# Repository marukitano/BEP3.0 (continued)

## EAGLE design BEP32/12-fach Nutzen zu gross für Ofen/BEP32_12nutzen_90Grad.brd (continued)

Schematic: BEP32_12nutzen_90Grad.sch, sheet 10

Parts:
6V1001, 10V1001: TPSB2.0; B2.0
19, 20: 2081-1132; 12-PIN
C1001: 4.7u; C0805
C1002, C1010: 100nF; C0805
C1003, C1004: 100nF,; C0805
C1005, C1006: 100nF.; C0805
C1007, C1008: 100u; C1206
C1009: 2.2nF; C0805
D1001: SM6T; DO214AA
D1002, D1003: 1N4007,; DO-214AC
D1004: SM6TDO214AA_BI; DO214AA_BI
D1005, D1006: 1N4007.; DO-214AC
D1007, D1010: 1N5817; DO-214AC_SLIM
D1008, D1009: 1N5817.; DO-214AC_SLIM
D1011, D1012: 1N4007; DO-214AC
FID1001, FID1002, FID1003, FID1004: FIDUCIAL; FIDUCIAL_1MM
IC1001: LM2904; SO08
IC1002: 78L06; SOT89_ROUND
IC1003: 6V pos; 78LXX
IC1004: 78L10; SOT89_ROUND
IC1005: 4028; SO16
IC1006: NUP4304SOT457_R; SOT457R_PHILIPS
IC1007: ULN2004; SO16
IC1008: LM339; SO14
IC1009: 317TO202H_NOHOLE; TO220H_NOHOLE
IC1010: 555; SO08
IC1011: 4538; SO16
JP1001, JP1002, JP1003, JP1004: JP2EJP2_SMALLPADS; JP2_SMALLPADS
JP1005: JP2E_ORIG; JP2_ORIG_SMALLPADS
LED1001, LED1002, LED1003, LED1004, LED1005, LED1006: LEDLD260; LD260
Q1001, Q1002: BA.; SOT89
Q1003: MY; SOT89
Q1004, Q1005: BA; SOT89
Q1006, Q1007: J1; SOT-23
R1001, R1012, R1013, R1014, R1028: 102; R0805
R1002, R1006, R1018, R1034: 13; R1206
R1003, R1004: R_user; R0805
R1005, R1016, R1026: 4701; R0805
R1007, R1008, R1020, R1024, R1032: 1002; R0805
R1009, R1010, R1011: 104.; R0805
R1015, R1038: 100; R0805
R1017, R1022, R1023, R1040, R1045: 2702; R0805
R1019, R1033: 2201; R0805
R1021, R1031: 1502; R0805
R1025, R1030, R1035, R1041: 104; R0805
R1027, R1029, R1036, R1037: 47; V235/17_1MM
R1039, R1043: (101); R0805
R1042: (1000); R0805
R1044, R1046: (1002); R0805
SJ1001: SJ
START1001: TPSB2.0; B2.0
TP208, TP209, TP210, TP211, TP212, TP213, TP214, TP215, TP216, TP217, TP218, TP219, TP220, TP221, TP222, TP223, TP224, TP225, TP227, TP228, TP229, TP230: TPSB2.0; B2.0
TP226: TPSB1,27; B1,27
X1001: CON_BMWV2; 24-PIN_V2
X1002: 22-23-2021
X1003: 22-23-2051

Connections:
+10V: 10V1001.TP, C1002.1, IC1004.1 (OUT), IC1010.4 (R), IC1010.8 (V+), IC1011.3 (CD), IC1011.5 (B), IC1011.13 (CD), IC1011.16 (VDD), R1045.2; also elsewhere on the board
+12V: 20.1, D1001.C, IC1002.3 (IN), IC1003.IN, IC1004.3 (IN), IC1005.16 (VDD), IC1006.2 (V+), IC1007.9 (CD+), JP1001.2, Q1004.3 (E), Q1005.3 (E), R1002.1, R1006.1, R1009.2, R1010.2, R1011.2, R1029.2, R1035.1, TP229.TP, X1001.6, X1003.1; also elsewhere on the board
+12V10: IC1001.7 (OUT), R1016.1, R1017.1
GND: 19.12, C1001.2, C1002.2, C1003.2, C1004.2, C1005.2, C1006.1, C1007.2, C1008.2, C1009.1, C1010.2, D1001.A, D1004.A, D1005.1 (+), IC1001.4 (V-), IC1002.2 (GND), IC1002.2@1 (GND), IC1003.GND, IC1004.2 (GND), IC1004.2@1 (GND), IC1005.8 (VSS), IC1005.11 (D), IC1006.5 (V-), IC1007.8 (GND), IC1008.10 (-IN), IC1008.11 (+IN), IC1008.12 (GND), IC1010.1 (GND), IC1011.1 (T1), IC1011.4 (A), IC1011.8 (VSS), IC1011.15 (T1), Q1003.3 (E), Q1006.2 (S), Q1007.2 (S), R1001.2, R1003.2, R1004.2, R1007.1, R1014.1, R1023.1, R1032.1, R1036.1, R1037.1, R1039.2, R1041.2, R1043.2, X1001.13, X1001.18, X1001.23, X1002.1, X1003.5; also elsewhere on the board
unnamed: R1027.2, R1029.1
unnamed: 20.9, D1007.1 (+), D1008.1 (+), JP1002.1, JP1003.2, TP226.TP
unnamed: IC1005.10 (A), IC1006.1 (D1), R1011.1, X1001.4, X1003.2
unnamed: IC1005.13 (B), IC1006.4 (D4), R1010.1, X1001.3, X1003.3
unnamed: D1005.2 (-), Q1004.2 (C), START1001.TP, X1001.5
unnamed: IC1005.12 (C), IC1006.3 (D3), R1009.1, X1001.2, X1003.4
unnamed: 20.7, LED1001.A, TP224.TP, X1001.8
unnamed: 20.2, D1009.2 (-), LED1002.K (C), TP219.TP, X1001.12
unnamed: 20.3, D1008.2 (-), LED1003.K (C), TP220.TP, X1001.11
unnamed: 20.4, D1007.2 (-), LED1004.K (C), TP221.TP, X1001.10
unnamed: 20.8, D1010.2 (-), LED1006.K (C), TP225.TP, X1001.14
unnamed: 19.9, D1002.1 (+), TP216.TP, X1001.17
unnamed: 19.11, D1003.1 (+), TP218.TP, X1001.19
unnamed: D1004.C, R1005.2, X1001.22
unnamed: C1001.1, IC1001.3 (+IN), R1005.1
unnamed: 20.11, IC1007.16 (O1), R1018.2, R1019.1, TP228.TP
unnamed: IC1008.1 (OUT), R1024.2, R1025.2
unnamed: C1007.1, R1025.1, R1030.2
unnamed: C1008.1, IC1008.4 (-IN), R1030.1
unnamed: IC1008.5 (+IN), R1031.1, R1032.2, R1033.2
unnamed: D1011.1 (+), R1033.1
unnamed: C1005.1, IC1008.9 (+IN), R1022.2, R1023.2
unnamed: C1006.2, IC1008.14 (OUT), R1026.2
unnamed: Q1005.1 (B), R1026.1
unnamed: IC1005.2 (Q2), IC1007.7 (I7)
unnamed: 19.5, IC1007.12 (O5), TP212.TP
unnamed: IC1005.1 (Q4), IC1007.4 (I4)
unnamed: 19.8, Q1006.3 (D), TP215.TP
unnamed: 20.10, TP227.TP, X1001.15
unnamed: 20.5, D1006.2 (-), LED1005.K (C), TP222.TP, X1001.9
unnamed: D1006.1 (+), R1027.1
unnamed: IC1005.6 (Q5), IC1007.3 (I3)
unnamed: 19.4, IC1007.10 (O7), TP211.TP
unnamed: IC1009.1 (ADJ), R1020.2, R1034.1, X1001.7
unnamed: IC1008.6 (-IN), IC1008.8 (-IN), R1020.1
unnamed: 19.2, Q1001.2 (C), TP209.TP
unnamed: 19.1, TP208.TP, X1001.1
unnamed: R1040.2, X1001.16
unnamed: IC1005.15 (Q3), IC1007.5 (I5)
unnamed: 19.6, IC1007.13 (O4), TP213.TP
unnamed: 19.7, IC1007.14 (O3), TP214.TP
unnamed: 20.6, JP1005.2, TP223.TP
unnamed: LED1001.K (C), R1043.1
unnamed: LED1002.A, LED1003.A, LED1004.A, LED1005.A, LED1006.A, R1042.1
unnamed: Q1004.1 (B), R1028.2
unnamed: IC1005.3 (Q0), IC1007.1 (I1), IC1007.2 (I2), Q1006.1 (G)
unnamed: IC1005.14 (Q1), IC1007.6 (I6)
unnamed: 19.3, IC1007.11 (O6), TP210.TP
unnamed: Q1001.1 (B), Q1002.1 (B), Q1002.2 (C), R1001.1, R1003.1, R1004.1, X1002.2
unnamed: Q1001.3 (E), R1002.2
unnamed: Q1002.3 (E), R1006.2
unnamed: IC1008.7 (+IN), R1021.1, R1022.1
unnamed: IC1001.2 (-IN), R1007.2
unnamed: Q1003.1 (B), R1016.2
unnamed: Q1007.3 (D), R1038.2
unnamed: IC1009.2 (VO), R1034.2
unnamed: IC1009.3 (VI), Q1005.2 (C)
unnamed: C1009.2, D1012.2 (-), IC1006.6 (D2), IC1010.2 (TR), IC1010.6 (THR), R1041.1
unnamed: IC1010.5 (CV), R1044.2
unnamed: IC1010.3 (Q), IC1011.12 (A), R1044.1
unnamed: D1012.1 (+), R1040.1
unnamed: 19.10, D1002.2 (-), D1003.2 (-), JP1004.1, SJ1001.1, TP217.TP
unnamed: JP1004.2, R1036.2, R1037.2, SJ1001.2
unnamed: IC1011.9 (!Q), IC1011.11 (B), R1046.2
unnamed: C1010.1, IC1011.14 (T2), R1045.1
unnamed: JP1001.1, R1019.2
unnamed: IC1007.15 (O2), R1028.1
unnamed: 20.12, R1046.1, TP230.TP
unnamed: D1009.1 (+), JP1002.2
unnamed: D1011.2 (-), IC1008.2 (OUT), JP1005.1, Q1007.1 (G), R1035.2
unnamed: IC1001.1 (OUT), R1008.2
unnamed: C1003.1, R1008.1, R1012.1
unnamed: IC1001.5 (+IN), R1012.2, R1017.2
unnamed: IC1001.6 (-IN), R1013.1, R1014.2
unnamed: D1010.1 (+), JP1003.1
unnamed: JP1005.3, R1038.1, R1039.1
unnamed: R1015.1, X1001.21
unnamed: Q1003.2 (C), R1015.2, R1018.1
VCC: 6V1001.TP, C1004.1, IC1001.8 (V+), IC1002.1 (OUT), IC1003.OUT, IC1008.3 (V+), R1013.2, R1021.2, R1024.1, R1031.2, R1042.2; also elsewhere on the board

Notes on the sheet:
6V regulated for Opamps
current source 96mA
ZündungsPlus
Zündugsplus Choke Öldrucklampe Temperaturlampe Ladekontrolllampe Tankgeber (100hm) ABS-Lampe Lampentest Warnlampe Fernlichtlampe Geschwindigkeitssignal Menütaster
DauerPlus Konstant-Strom für LEDs Gang 1 Gang 2 Gang 3 Gang 4 Gang 5 Neutrallampe Blinker rechts Blinker zusammen Blinker links Masse
DauerPlus Batterie 12V (rot weiss) Ganganzeige Signal C (gelb weiss) Ganganzeige Signal B (gelb schwarz) Ganganzeige Signal A (gelb dunkelblau) 12V/350mA zum Starknopf (schwarz grün) Zündungsplus 12V (grün schwarz) Reservelampe (weiss) ABS Leuchte (blau) Ladekontrollleuchte (schaltet auf Masse) (vi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
Masse (braun) Lampentest (schaltet auf Masse)(weiss blau) Fernlichtlampe (12V) (weiss) Drehzahl Zündspule (schwarz blau) Blinker rechts (blau scharz) Masse (braun) Blinker links (blau rot) nicht angeschlossen Tachosiganl zum Blinrelais (balu grün) Tachogeber (gelb) Masse Tachobeger (braun) Tachobel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
4.7V
Stromquelle für Gang LEDs. Für mehr als 12mA muss ein Widerstand "R_user" eingelötet werden. Für weniger muss der 1kOhm SMD Widerstand neben R_user entfernt werden I = 12V/1kOhm(default)+12V/R_user I= 12mA (default) + 12V/R_user Beispiel: R_user Strom in LEDs 1 kOhm 22-26mA ohne 11-13mA
Gang 1
Gang 2
Gang 3
Gang 4
Gang 5
Variante "eine LED leuchtet"
Variante "alle LEDs bis und mit Gang X leuchten"
Klemmleisten Ausgang:
Klemmleisten Ausgang:
an Zündungsplus anhängen (Neutral leuchtet wenn Gang 0 eingelegt und Zündschlüssel steckt )
an Ausgang "Neutrallampe" anhängen
Neutrallampe für eigene Ganganzeige
Externe Beschaltung
Anzeige:
nicht bestückt
rising edge trigger A
BAR
RES
BL resistors

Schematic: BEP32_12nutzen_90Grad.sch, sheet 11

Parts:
6V1101, 10V1101: TPSB2.0; B2.0
21, 22: 2081-1132; 12-PIN
C1101: 4.7u; C0805
C1102, C1110: 100nF; C0805
C1103, C1104: 100nF,; C0805
C1105, C1106: 100nF.; C0805
C1107, C1108: 100u; C1206
C1109: 2.2nF; C0805
D1101: SM6T; DO214AA
D1102, D1103: 1N4007,; DO-214AC
D1104: SM6TDO214AA_BI; DO214AA_BI
D1105, D1106: 1N4007.; DO-214AC
D1107, D1110: 1N5817; DO-214AC_SLIM
D1108, D1109: 1N5817.; DO-214AC_SLIM
D1111, D1112: 1N4007; DO-214AC
FID1101, FID1102, FID1103, FID1104: FIDUCIAL; FIDUCIAL_1MM
IC1101: LM2904; SO08
IC1102: 78L06; SOT89_ROUND
IC1103: 6V pos; 78LXX
IC1104: 78L10; SOT89_ROUND
IC1105: 4028; SO16
IC1106: NUP4304SOT457_R; SOT457R_PHILIPS
IC1107: ULN2004; SO16
IC1108: LM339; SO14
IC1109: 317TO202H_NOHOLE; TO220H_NOHOLE
IC1110: 555; SO08
IC1111: 4538; SO16
JP1101, JP1102, JP1103, JP1104: JP2EJP2_SMALLPADS; JP2_SMALLPADS
JP1105: JP2E_ORIG; JP2_ORIG_SMALLPADS
LED1101, LED1102, LED1103, LED1104, LED1105, LED1106: LEDLD260; LD260
Q1101, Q1102: BA.; SOT89
Q1103: MY; SOT89
Q1104, Q1105: BA; SOT89
Q1106, Q1107: J1; SOT-23
R1101, R1112, R1113, R1114, R1128: 102; R0805
R1102, R1106, R1118, R1134: 13; R1206
R1103, R1104: R_user; R0805
R1105, R1116, R1126: 4701; R0805
R1107, R1108, R1120, R1124, R1132: 1002; R0805
R1109, R1110, R1111, R1135: 104.; R0805
R1115, R1138: 100; R0805
R1117, R1122, R1123, R1140, R1145: 2702; R0805
R1119, R1133: 2201; R0805
R1121, R1131: 1502; R0805
R1125, R1130, R1141: 104; R0805
R1127, R1129, R1136, R1137: 47; V235/17_1MM
R1139, R1143: (101); R0805
R1142: (1000); R0805
R1144, R1146: (1002); R0805
SJ1101: SJ
START1101: TPSB2.0; B2.0
TP231, TP232, TP233, TP234, TP235, TP236, TP237, TP238, TP239, TP240, TP241, TP242, TP243, TP244, TP245, TP246, TP247, TP248, TP250, TP251, TP252, TP253: TPSB2.0; B2.0
TP249: TPSB1,27; B1,27
X1101: CON_BMWV2; 24-PIN_V2
X1102: 22-23-2021
X1103: 22-23-2051

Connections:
+10V: 10V1101.TP, C1102.1, IC1104.1 (OUT), IC1110.4 (R), IC1110.8 (V+), IC1111.3 (CD), IC1111.5 (B), IC1111.13 (CD), IC1111.16 (VDD), R1145.2; also elsewhere on the board
+12V: 22.1, D1101.C, IC1102.3 (IN), IC1103.IN, IC1104.3 (IN), IC1105.16 (VDD), IC1106.2 (V+), IC1107.9 (CD+), JP1101.2, Q1104.3 (E), Q1105.3 (E), R1102.1, R1106.1, R1109.2, R1110.2, R1111.2, R1129.2, R1135.1, TP252.TP, X1101.6, X1103.1; also elsewhere on the board
+12V11: IC1101.7 (OUT), R1116.1, R1117.1
GND: 21.12, C1101.2, C1102.2, C1103.2, C1104.2, C1105.2, C1106.1, C1107.2, C1108.2, C1109.1, C1110.2, D1101.A, D1104.A, D1105.1 (+), IC1101.4 (V-), IC1102.2 (GND), IC1102.2@1 (GND), IC1103.GND, IC1104.2 (GND), IC1104.2@1 (GND), IC1105.8 (VSS), IC1105.11 (D), IC1106.5 (V-), IC1107.8 (GND), IC1108.10 (-IN), IC1108.11 (+IN), IC1108.12 (GND), IC1110.1 (GND), IC1111.1 (T1), IC1111.4 (A), IC1111.8 (VSS), IC1111.15 (T1), Q1103.3 (E), Q1106.2 (S), Q1107.2 (S), R1101.2, R1103.2, R1104.2, R1107.1, R1114.1, R1123.1, R1132.1, R1136.1, R1137.1, R1139.2, R1141.2, R1143.2, X1101.13, X1101.18, X1101.23, X1102.1, X1103.5; also elsewhere on the board
unnamed: R1127.2, R1129.1
unnamed: 22.9, D1107.1 (+), D1108.1 (+), JP1102.1, JP1103.2, TP249.TP
unnamed: IC1105.10 (A), IC1106.1 (D1), R1111.1, X1101.4, X1103.2
unnamed: IC1105.13 (B), IC1106.4 (D4), R1110.1, X1101.3, X1103.3
unnamed: D1105.2 (-), Q1104.2 (C), START1101.TP, X1101.5
unnamed: IC1105.12 (C), IC1106.3 (D3), R1109.1, X1101.2, X1103.4
unnamed: 22.7, LED1101.A, TP247.TP, X1101.8
unnamed: 22.2, D1109.2 (-), LED1102.K (C), TP242.TP, X1101.12
unnamed: 22.3, D1108.2 (-), LED1103.K (C), TP243.TP, X1101.11
unnamed: 22.4, D1107.2 (-), LED1104.K (C), TP244.TP, X1101.10
unnamed: 22.8, D1110.2 (-), LED1106.K (C), TP248.TP, X1101.14
unnamed: 21.9, D1102.1 (+), TP239.TP, X1101.17
unnamed: 21.11, D1103.1 (+), TP241.TP, X1101.19
unnamed: D1104.C, R1105.2, X1101.22
unnamed: C1101.1, IC1101.3 (+IN), R1105.1
unnamed: 22.11, IC1107.16 (O1), R1118.2, R1119.1, TP251.TP
unnamed: IC1108.1 (OUT), R1124.2, R1125.2
unnamed: C1107.1, R1125.1, R1130.2
unnamed: C1108.1, IC1108.4 (-IN), R1130.1
unnamed: IC1108.5 (+IN), R1131.1, R1132.2, R1133.2
unnamed: D1111.1 (+), R1133.1
unnamed: C1105.1, IC1108.9 (+IN), R1122.2, R1123.2
unnamed: C1106.2, IC1108.14 (OUT), R1126.2
unnamed: Q1105.1 (B), R1126.1
unnamed: IC1105.2 (Q2), IC1107.7 (I7)
unnamed: 21.5, IC1107.12 (O5), TP235.TP
unnamed: IC1105.1 (Q4), IC1107.4 (I4)
unnamed: 21.8, Q1106.3 (D), TP238.TP
unnamed: 22.10, TP250.TP, X1101.15
unnamed: 22.5, D1106.2 (-), LED1105.K (C), TP245.TP, X1101.9
unnamed: D1106.1 (+), R1127.1
unnamed: IC1105.6 (Q5), IC1107.3 (I3)
unnamed: 21.4, IC1107.10 (O7), TP234.TP
unnamed: IC1109.1 (ADJ), R1120.2, R1134.1, X1101.7
unnamed: IC1108.6 (-IN), IC1108.8 (-IN), R1120.1
unnamed: 21.2, Q1101.2 (C), TP232.TP
unnamed: 21.1, TP231.TP, X1101.1
unnamed: R1140.2, X1101.16
unnamed: IC1105.15 (Q3), IC1107.5 (I5)
unnamed: 21.6, IC1107.13 (O4), TP236.TP
unnamed: 21.7, IC1107.14 (O3), TP237.TP
unnamed: 22.6, JP1105.2, TP246.TP
unnamed: LED1101.K (C), R1143.1
unnamed: LED1102.A, LED1103.A, LED1104.A, LED1105.A, LED1106.A, R1142.1
unnamed: Q1104.1 (B), R1128.2
unnamed: IC1105.3 (Q0), IC1107.1 (I1), IC1107.2 (I2), Q1106.1 (G)
unnamed: IC1105.14 (Q1), IC1107.6 (I6)
unnamed: 21.3, IC1107.11 (O6), TP233.TP
unnamed: Q1101.1 (B), Q1102.1 (B), Q1102.2 (C), R1101.1, R1103.1, R1104.1, X1102.2
unnamed: Q1101.3 (E), R1102.2
unnamed: Q1102.3 (E), R1106.2
unnamed: IC1108.7 (+IN), R1121.1, R1122.1
unnamed: IC1101.2 (-IN), R1107.2
unnamed: Q1103.1 (B), R1116.2
unnamed: Q1107.3 (D), R1138.2
unnamed: IC1109.2 (VO), R1134.2
unnamed: IC1109.3 (VI), Q1105.2 (C)
unnamed: C1109.2, D1112.2 (-), IC1106.6 (D2), IC1110.2 (TR), IC1110.6 (THR), R1141.1
unnamed: IC1110.5 (CV), R1144.2
unnamed: IC1110.3 (Q), IC1111.12 (A), R1144.1
unnamed: D1112.1 (+), R1140.1
unnamed: 21.10, D1102.2 (-), D1103.2 (-), JP1104.1, SJ1101.1, TP240.TP
unnamed: JP1104.2, R1136.2, R1137.2, SJ1101.2
unnamed: IC1111.9 (!Q), IC1111.11 (B), R1146.2
unnamed: C1110.1, IC1111.14 (T2), R1145.1
unnamed: JP1101.1, R1119.2
unnamed: IC1107.15 (O2), R1128.1
unnamed: 22.12, R1146.1, TP253.TP
unnamed: D1109.1 (+), JP1102.2
unnamed: D1111.2 (-), IC1108.2 (OUT), JP1105.1, Q1107.1 (G), R1135.2
unnamed: IC1101.1 (OUT), R1108.2
unnamed: C1103.1, R1108.1, R1112.1
unnamed: IC1101.5 (+IN), R1112.2, R1117.2
unnamed: IC1101.6 (-IN), R1113.1, R1114.2
unnamed: D1110.1 (+), JP1103.1
unnamed: JP1105.3, R1138.1, R1139.1
unnamed: R1115.1, X1101.21
unnamed: Q1103.2 (C), R1115.2, R1118.1
VCC: 6V1101.TP, C1104.1, IC1101.8 (V+), IC1102.1 (OUT), IC1103.OUT, IC1108.3 (V+), R1113.2, R1121.2, R1124.1, R1131.2, R1142.2; also elsewhere on the board

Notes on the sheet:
6V regulated for Opamps
current source 96mA
ZündungsPlus
Zündugsplus Choke Öldrucklampe Temperaturlampe Ladekontrolllampe Tankgeber (100hm) ABS-Lampe Lampentest Warnlampe Fernlichtlampe Geschwindigkeitssignal Menütaster
DauerPlus Konstant-Strom für LEDs Gang 1 Gang 2 Gang 3 Gang 4 Gang 5 Neutrallampe Blinker rechts Blinker zusammen Blinker links Masse
DauerPlus Batterie 12V (rot weiss) Ganganzeige Signal C (gelb weiss) Ganganzeige Signal B (gelb schwarz) Ganganzeige Signal A (gelb dunkelblau) 12V/350mA zum Starknopf (schwarz grün) Zündungsplus 12V (grün schwarz) Reservelampe (weiss) ABS Leuchte (blau) Ladekontrollleuchte (schaltet auf Masse) (vi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
Masse (braun) Lampentest (schaltet auf Masse)(weiss blau) Fernlichtlampe (12V) (weiss) Drehzahl Zündspule (schwarz blau) Blinker rechts (blau scharz) Masse (braun) Blinker links (blau rot) nicht angeschlossen Tachosiganl zum Blinrelais (balu grün) Tachogeber (gelb) Masse Tachobeger (braun) Tachobel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
4.7V
Stromquelle für Gang LEDs. Für mehr als 12mA muss ein Widerstand "R_user" eingelötet werden. Für weniger muss der 1kOhm SMD Widerstand neben R_user entfernt werden I = 12V/1kOhm(default)+12V/R_user I= 12mA (default) + 12V/R_user Beispiel: R_user Strom in LEDs 1 kOhm 22-26mA ohne 11-13mA
Gang 1
Gang 2
Gang 3
Gang 4
Gang 5
Variante "eine LED leuchtet"
Variante "alle LEDs bis und mit Gang X leuchten"
Klemmleisten Ausgang:
Klemmleisten Ausgang:
an Zündungsplus anhängen (Neutral leuchtet wenn Gang 0 eingelegt und Zündschlüssel steckt )
an Ausgang "Neutrallampe" anhängen
Neutrallampe für eigene Ganganzeige
Externe Beschaltung
Anzeige:
nicht bestückt
rising edge trigger A
BAR
RES
BL resistors

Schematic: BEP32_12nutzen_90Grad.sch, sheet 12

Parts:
6V1201, 10V1201: TPSB2.0; B2.0
23, 24: 2081-1132; 12-PIN
C1201: 4.7u; C0805
C1202, C1210: 100nF; C0805
C1203, C1204: 100nF,; C0805
C1205, C1206: 100nF.; C0805
C1207, C1208: 100u; C1206
C1209: 2.2nF; C0805
D1201: SM6T; DO214AA
D1202, D1203: 1N4007,; DO-214AC
D1204: SM6TDO214AA_BI; DO214AA_BI
D1205, D1206: 1N4007.; DO-214AC
D1207, D1210: 1N5817; DO-214AC_SLIM
D1208, D1209: 1N5817.; DO-214AC_SLIM
D1211, D1212: 1N4007; DO-214AC
FID1201, FID1202, FID1203, FID1204: FIDUCIAL; FIDUCIAL_1MM
IC1201: LM2904; SO08
IC1202: 78L06; SOT89_ROUND
IC1203: 6V pos; 78LXX
IC1204: 78L10; SOT89_ROUND
IC1205: 4028; SO16
IC1206: NUP4304SOT457_R; SOT457R_PHILIPS
IC1207: ULN2004; SO16
IC1208: LM339; SO14
IC1209: 317TO202H_NOHOLE; TO220H_NOHOLE
IC1210: 555; SO08
IC1211: 4538; SO16
JP1201, JP1202, JP1203, JP1204: JP2EJP2_SMALLPADS; JP2_SMALLPADS
JP1205: JP2E_ORIG; JP2_ORIG_SMALLPADS
LED1201, LED1202, LED1203, LED1204, LED1205, LED1206: LEDLD260; LD260
Q1201, Q1202: BA.; SOT89
Q1203: MY; SOT89
Q1204, Q1205: BA; SOT89
Q1206, Q1207: J1; SOT-23
R1201, R1212, R1213, R1214, R1228: 102; R0805
R1202, R1206, R1218, R1234: 13; R1206
R1203, R1204: R_user; R0805
R1205, R1216, R1226: 4701; R0805
R1207, R1208, R1220, R1224, R1232: 1002; R0805
R1209, R1210, R1211: 104.; R0805
R1215, R1238: 100; R0805
R1217, R1222, R1223, R1240, R1245: 2702; R0805
R1219, R1233: 2201; R0805
R1221, R1231: 1502; R0805
R1225, R1230, R1235, R1241: 104; R0805
R1227, R1229, R1236, R1237: 47; V235/17_1MM
R1239, R1243: (101); R0805
R1242: (1000); R0805
R1244, R1246: (1002); R0805
SJ1201: SJ
START1201: TPSB2.0; B2.0
TP254, TP255, TP256, TP257, TP258, TP259, TP260, TP261, TP262, TP263, TP264, TP265, TP266, TP267, TP268, TP269, TP270, TP271, TP273, TP274, TP275, TP276: TPSB2.0; B2.0
TP272: TPSB1,27; B1,27
X1201: CON_BMWV2; 24-PIN_V2
X1202: 22-23-2021
X1203: 22-23-2051

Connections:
+10V: 10V1201.TP, C1202.1, IC1204.1 (OUT), IC1210.4 (R), IC1210.8 (V+), IC1211.3 (CD), IC1211.5 (B), IC1211.13 (CD), IC1211.16 (VDD), R1245.2; also elsewhere on the board
+12V: 24.1, D1201.C, IC1202.3 (IN), IC1203.IN, IC1204.3 (IN), IC1205.16 (VDD), IC1206.2 (V+), IC1207.9 (CD+), JP1201.2, Q1204.3 (E), Q1205.3 (E), R1202.1, R1206.1, R1209.2, R1210.2, R1211.2, R1229.2, R1235.1, TP275.TP, X1201.6, X1203.1; also elsewhere on the board
+12V12: IC1201.7 (OUT), R1216.1, R1217.1
GND: 23.12, C1201.2, C1202.2, C1203.2, C1204.2, C1205.2, C1206.1, C1207.2, C1208.2, C1209.1, C1210.2, D1201.A, D1204.A, D1205.1 (+), IC1201.4 (V-), IC1202.2 (GND), IC1202.2@1 (GND), IC1203.GND, IC1204.2 (GND), IC1204.2@1 (GND), IC1205.8 (VSS), IC1205.11 (D), IC1206.5 (V-), IC1207.8 (GND), IC1208.10 (-IN), IC1208.11 (+IN), IC1208.12 (GND), IC1210.1 (GND), IC1211.1 (T1), IC1211.4 (A), IC1211.8 (VSS), IC1211.15 (T1), Q1203.3 (E), Q1206.2 (S), Q1207.2 (S), R1201.2, R1203.2, R1204.2, R1207.1, R1214.1, R1223.1, R1232.1, R1236.1, R1237.1, R1239.2, R1241.2, R1243.2, X1201.13, X1201.18, X1201.23, X1202.1, X1203.5; also elsewhere on the board
unnamed: R1227.2, R1229.1
unnamed: 24.9, D1207.1 (+), D1208.1 (+), JP1202.1, JP1203.2, TP272.TP
unnamed: IC1205.10 (A), IC1206.1 (D1), R1211.1, X1201.4, X1203.2
unnamed: IC1205.13 (B), IC1206.4 (D4), R1210.1, X1201.3, X1203.3
unnamed: D1205.2 (-), Q1204.2 (C), START1201.TP, X1201.5
unnamed: IC1205.12 (C), IC1206.3 (D3), R1209.1, X1201.2, X1203.4
unnamed: 24.7, LED1201.A, TP270.TP, X1201.8
unnamed: 24.2, D1209.2 (-), LED1202.K (C), TP265.TP, X1201.12
unnamed: 24.3, D1208.2 (-), LED1203.K (C), TP266.TP, X1201.11
unnamed: 24.4, D1207.2 (-), LED1204.K (C), TP267.TP, X1201.10
unnamed: 24.8, D1210.2 (-), LED1206.K (C), TP271.TP, X1201.14
unnamed: 23.9, D1202.1 (+), TP262.TP, X1201.17
unnamed: 23.11, D1203.1 (+), TP264.TP, X1201.19
unnamed: D1204.C, R1205.2, X1201.22
unnamed: C1201.1, IC1201.3 (+IN), R1205.1
unnamed: 24.11, IC1207.16 (O1), R1218.2, R1219.1, TP274.TP
unnamed: IC1208.1 (OUT), R1224.2, R1225.2
unnamed: C1207.1, R1225.1, R1230.2
unnamed: C1208.1, IC1208.4 (-IN), R1230.1
unnamed: IC1208.5 (+IN), R1231.1, R1232.2, R1233.2
unnamed: D1211.1 (+), R1233.1
unnamed: C1205.1, IC1208.9 (+IN), R1222.2, R1223.2
unnamed: C1206.2, IC1208.14 (OUT), R1226.2
unnamed: Q1205.1 (B), R1226.1
unnamed: IC1205.2 (Q2), IC1207.7 (I7)
unnamed: 23.5, IC1207.12 (O5), TP258.TP
unnamed: IC1205.1 (Q4), IC1207.4 (I4)
unnamed: 23.8, Q1206.3 (D), TP261.TP
unnamed: 24.10, TP273.TP, X1201.15
unnamed: 24.5, D1206.2 (-), LED1205.K (C), TP268.TP, X1201.9
unnamed: D1206.1 (+), R1227.1
unnamed: IC1205.6 (Q5), IC1207.3 (I3)
unnamed: 23.4, IC1207.10 (O7), TP257.TP
unnamed: IC1209.1 (ADJ), R1220.2, R1234.1, X1201.7
unnamed: IC1208.6 (-IN), IC1208.8 (-IN), R1220.1
unnamed: 23.2, Q1201.2 (C), TP255.TP
unnamed: 23.1, TP254.TP, X1201.1
unnamed: R1240.2, X1201.16
unnamed: IC1205.15 (Q3), IC1207.5 (I5)
unnamed: 23.6, IC1207.13 (O4), TP259.TP
unnamed: 23.7, IC1207.14 (O3), TP260.TP
unnamed: 24.6, JP1205.2, TP269.TP
unnamed: LED1201.K (C), R1243.1
unnamed: LED1202.A, LED1203.A, LED1204.A, LED1205.A, LED1206.A, R1242.1
unnamed: Q1204.1 (B), R1228.2
unnamed: IC1205.3 (Q0), IC1207.1 (I1), IC1207.2 (I2), Q1206.1 (G)
unnamed: IC1205.14 (Q1), IC1207.6 (I6)
unnamed: 23.3, IC1207.11 (O6), TP256.TP
unnamed: Q1201.1 (B), Q1202.1 (B), Q1202.2 (C), R1201.1, R1203.1, R1204.1, X1202.2
unnamed: Q1201.3 (E), R1202.2
unnamed: Q1202.3 (E), R1206.2
unnamed: IC1208.7 (+IN), R1221.1, R1222.1
unnamed: IC1201.2 (-IN), R1207.2
unnamed: Q1203.1 (B), R1216.2
unnamed: Q1207.3 (D), R1238.2
unnamed: IC1209.2 (VO), R1234.2
unnamed: IC1209.3 (VI), Q1205.2 (C)
unnamed: C1209.2, D1212.2 (-), IC1206.6 (D2), IC1210.2 (TR), IC1210.6 (THR), R1241.1
unnamed: IC1210.5 (CV), R1244.2
unnamed: IC1210.3 (Q), IC1211.12 (A), R1244.1
unnamed: D1212.1 (+), R1240.1
unnamed: 23.10, D1202.2 (-), D1203.2 (-), JP1204.1, SJ1201.1, TP263.TP
unnamed: JP1204.2, R1236.2, R1237.2, SJ1201.2
unnamed: IC1211.9 (!Q), IC1211.11 (B), R1246.2
unnamed: C1210.1, IC1211.14 (T2), R1245.1
unnamed: JP1201.1, R1219.2
unnamed: IC1207.15 (O2), R1228.1
unnamed: 24.12, R1246.1, TP276.TP
unnamed: D1209.1 (+), JP1202.2
unnamed: D1211.2 (-), IC1208.2 (OUT), JP1205.1, Q1207.1 (G), R1235.2
unnamed: IC1201.1 (OUT), R1208.2
unnamed: C1203.1, R1208.1, R1212.1
unnamed: IC1201.5 (+IN), R1212.2, R1217.2
unnamed: IC1201.6 (-IN), R1213.1, R1214.2
unnamed: D1210.1 (+), JP1203.1
unnamed: JP1205.3, R1238.1, R1239.1
unnamed: R1215.1, X1201.21
unnamed: Q1203.2 (C), R1215.2, R1218.1
VCC: 6V1201.TP, C1204.1, IC1201.8 (V+), IC1202.1 (OUT), IC1203.OUT, IC1208.3 (V+), R1213.2, R1221.2, R1224.1, R1231.2, R1242.2; also elsewhere on the board

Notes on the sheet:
6V regulated for Opamps
current source 96mA
ZündungsPlus
Zündugsplus Choke Öldrucklampe Temperaturlampe Ladekontrolllampe Tankgeber (100hm) ABS-Lampe Lampentest Warnlampe Fernlichtlampe Geschwindigkeitssignal Menütaster
DauerPlus Konstant-Strom für LEDs Gang 1 Gang 2 Gang 3 Gang 4 Gang 5 Neutrallampe Blinker rechts Blinker zusammen Blinker links Masse
DauerPlus Batterie 12V (rot weiss) Ganganzeige Signal C (gelb weiss) Ganganzeige Signal B (gelb schwarz) Ganganzeige Signal A (gelb dunkelblau) 12V/350mA zum Starknopf (schwarz grün) Zündungsplus 12V (grün schwarz) Reservelampe (weiss) ABS Leuchte (blau) Ladekontrollleuchte (schaltet auf Masse) (vi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
Masse (braun) Lampentest (schaltet auf Masse)(weiss blau) Fernlichtlampe (12V) (weiss) Drehzahl Zündspule (schwarz blau) Blinker rechts (blau scharz) Masse (braun) Blinker links (blau rot) nicht angeschlossen Tachosiganl zum Blinrelais (balu grün) Tachogeber (gelb) Masse Tachobeger (braun) Tachobel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
4.7V
Stromquelle für Gang LEDs. Für mehr als 12mA muss ein Widerstand "R_user" eingelötet werden. Für weniger muss der 1kOhm SMD Widerstand neben R_user entfernt werden I = 12V/1kOhm(default)+12V/R_user I= 12mA (default) + 12V/R_user Beispiel: R_user Strom in LEDs 1 kOhm 22-26mA ohne 11-13mA
Gang 1
Gang 2
Gang 3
Gang 4
Gang 5
Variante "eine LED leuchtet"
Variante "alle LEDs bis und mit Gang X leuchten"
Klemmleisten Ausgang:
Klemmleisten Ausgang:
an Zündungsplus anhängen (Neutral leuchtet wenn Gang 0 eingelegt und Zündschlüssel steckt )
an Ausgang "Neutrallampe" anhängen
Neutrallampe für eigene Ganganzeige
Externe Beschaltung
Anzeige:
nicht bestückt
rising edge trigger A
BAR
RES
BL resistors

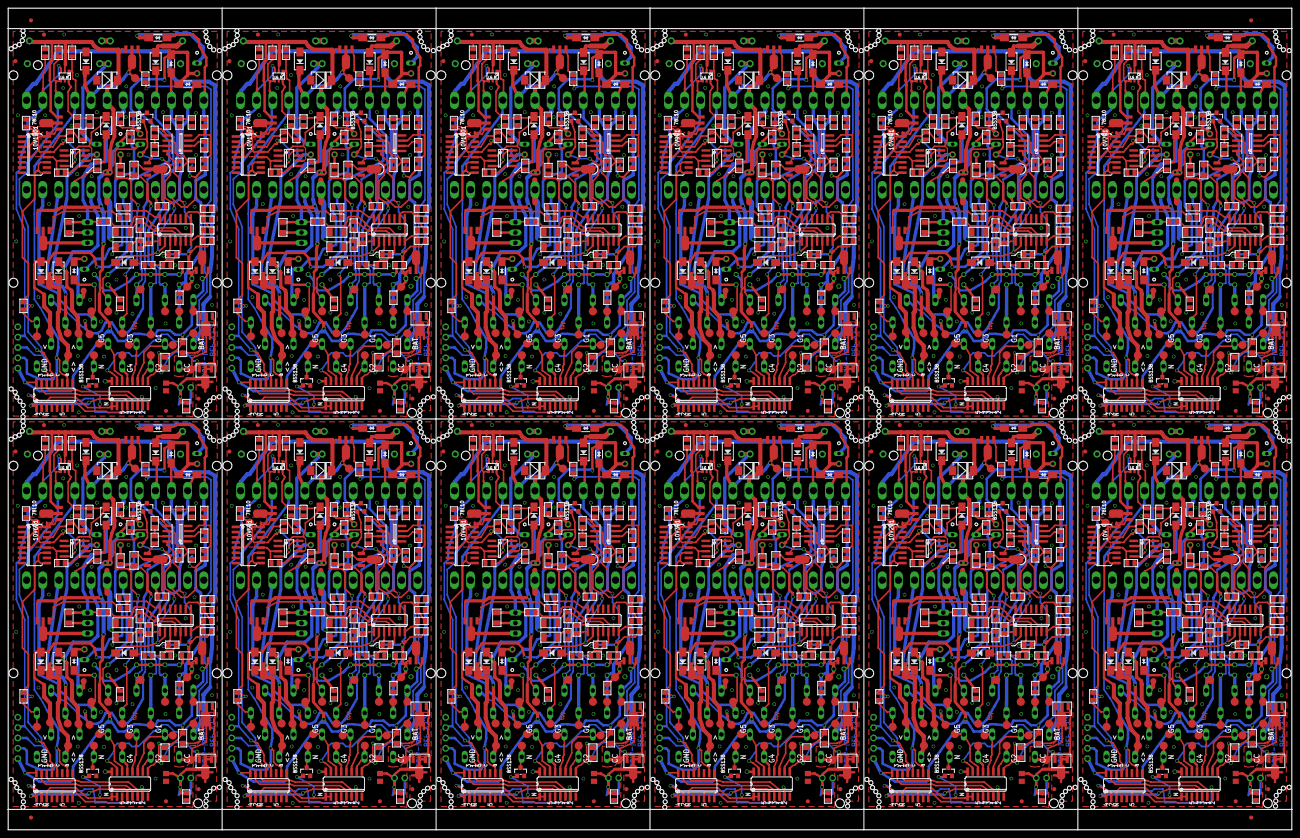
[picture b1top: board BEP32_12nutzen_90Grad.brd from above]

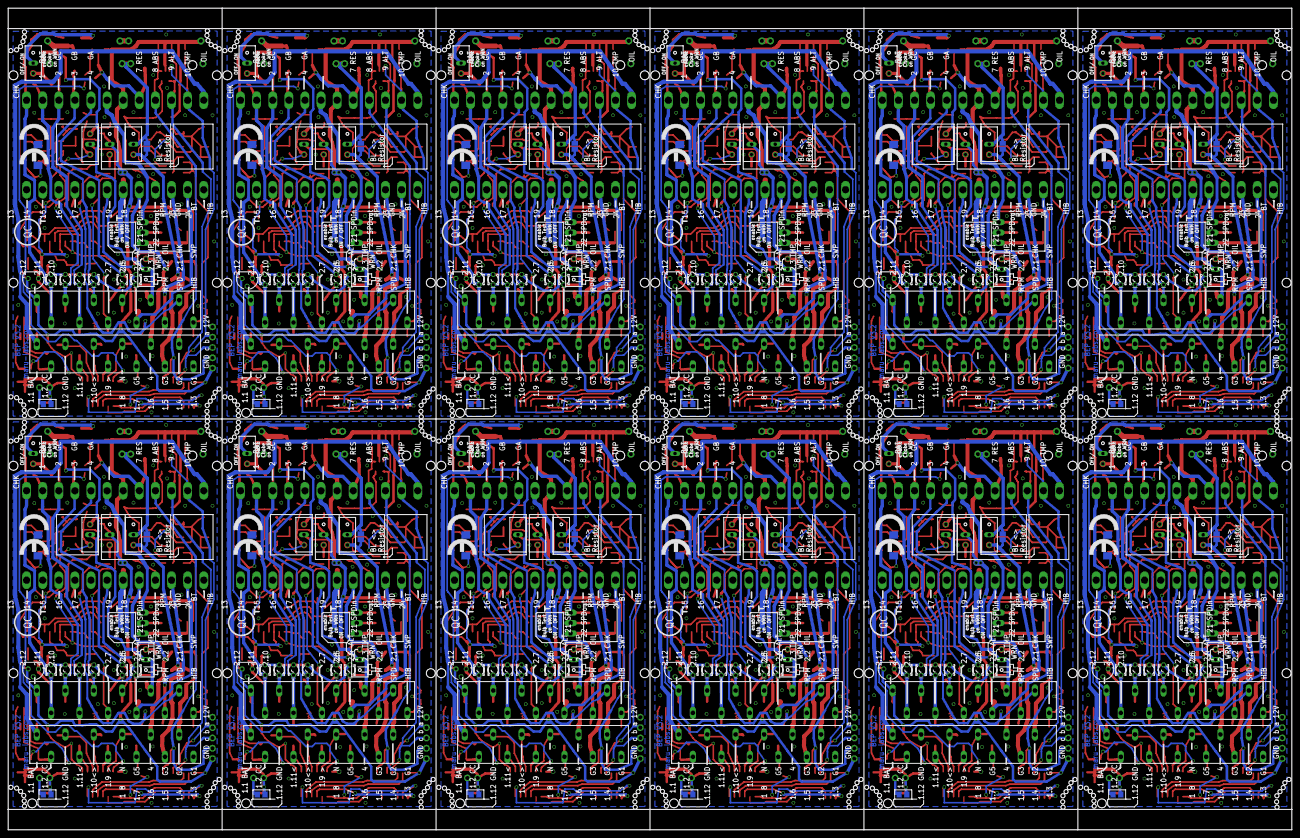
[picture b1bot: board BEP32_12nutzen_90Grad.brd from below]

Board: 2 copper layers, 315.6 x 202.0 mm, 1612 parts (312 on the bottom side), 952 nets.

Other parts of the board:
U$1, U$2, U$3, U$4, U$5, U$6, U$7, U$8, U$9, U$10, U$11, U$12: CE_10.00
